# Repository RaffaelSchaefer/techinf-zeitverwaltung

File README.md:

# Techinf Zeitverwaltung

---

## Grundidee

Unsere Idee war es, ein kleines und kompaktes System zu entwickeln, um die Arbeitszeit in Coworking-Spaces oder im Homeoffice zu erfassen.

## Getting Started

### Firmware

Es werden folgende Pakete im Projekt verwendet, die im Nachhinein installiert werden müssen:

- MFRC522
- ArduinoJson

Es müssen ein Verzeichnis namens `.env` erstellt werden. Danach müssen zwei Dateien erstellt werden.

**api.h**

```h
#define API_ADDRESS "Server Adresse"
#define API_KEY "API Passwort"
```

**credentials.h**

```h
#define SSID "SSID"
#define PASSWORD "Passwort"
```

Danach kann `firmware.ino` auf dem ESP 8266 geflasht werden.

### Server

Es gibt zwei Möglichkeiten den Server laufen zulassen. Einmal per Terminal oder via einen Docker Container.

#### Nutzung via Terminal (MacOS/Linux)

**1**: In den Server Ordner wechseln

```bash
cd ./server
```

**2**: Alle Module installieren die gebraucht werden

```bash
pip install -r requirements.txt
```

**3**: Die Datenbank initialisieren

```bash
python main.py -i
```

(**4**: Die Demo Daten hinzufügen)

```bash
python main.py -add
```

**5**: Server starten

```bash
python main.py -a 0.0.0.0 -p [port]
```

#### Nutzung via Docker (MacOS/Linux)

**1**: In den Server Ordner wechseln

```bash
cd ./server
```

**2**: Docker image erstellen

```bash
docker build -t [image_name] .
```

**3**: Docker Container starten

```bash
 docker run -d -p 80:80 --name [container_name] [image_name]
```

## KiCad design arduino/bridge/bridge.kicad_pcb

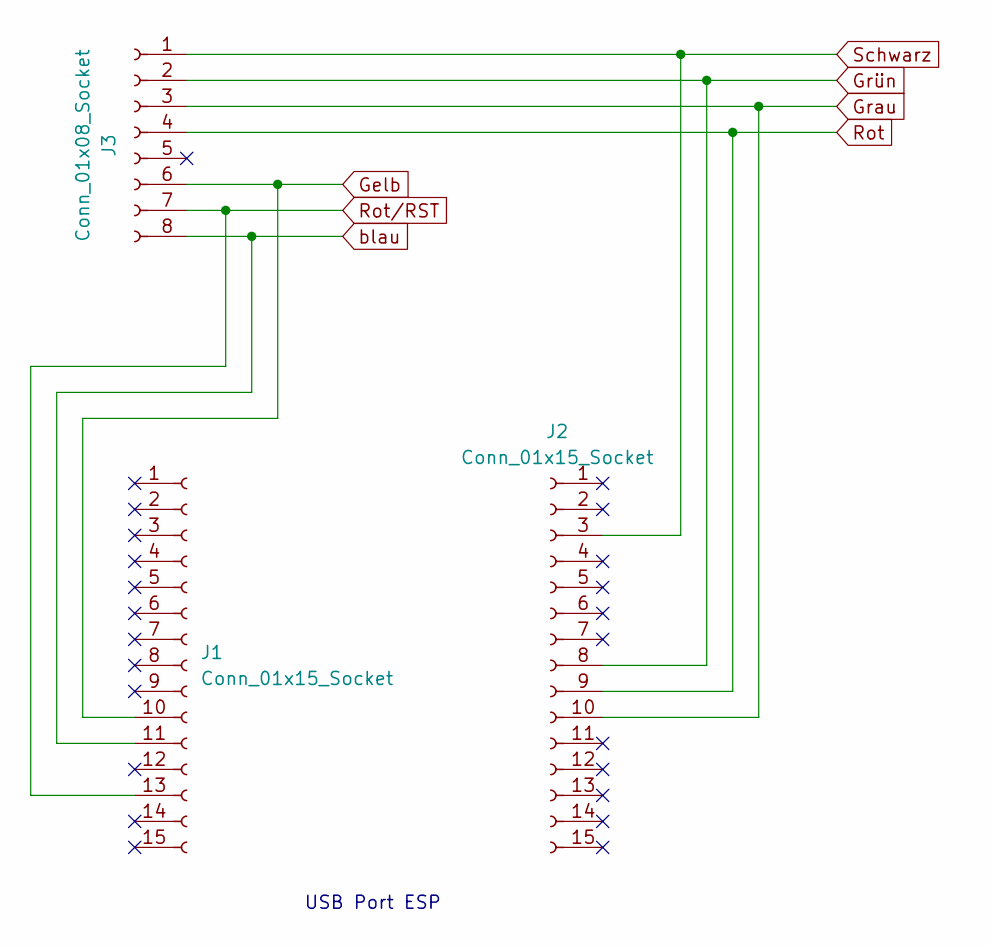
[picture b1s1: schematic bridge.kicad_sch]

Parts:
J1, J2: Conn_01x15_Socket; PinSocket_1x15_P2.54mm_Vertical
J3: Conn_01x08_Socket; PinSocket_1x08_P2.54mm_Vertical

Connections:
Gelb: J1.10, J3.6
Grau: J2.10, J3.3
Grün: J2.8, J3.2
Rot: J2.9, J3.4
Rot/RST: J1.13, J3.7
Schwarz: J2.3, J3.1
blau: J1.11, J3.8

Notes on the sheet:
USB Port ESP

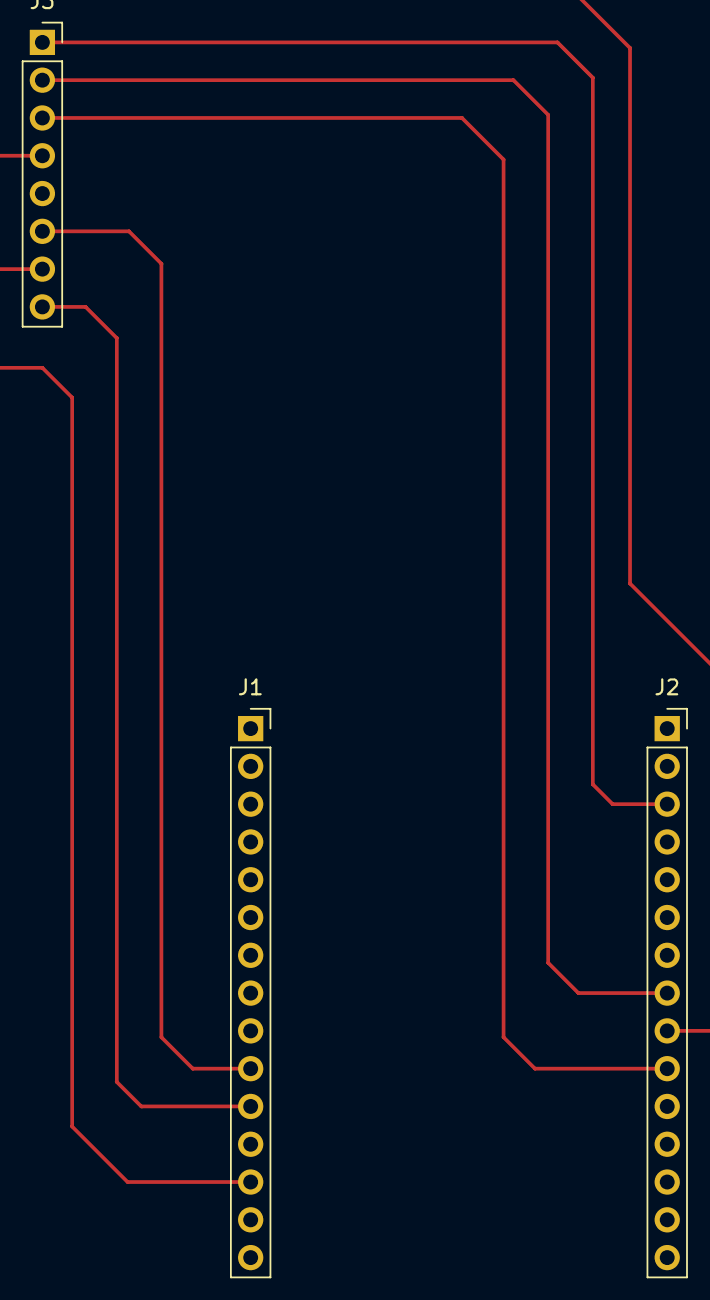
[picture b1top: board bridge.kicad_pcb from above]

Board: 2 copper layers, 3 parts (0 on the bottom side), 7 nets.

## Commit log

2023-12-14 Removed Placeholder and inserted Placeholder
2023-12-19 doc: Added docs
    Imported them as a backup from Overleaf. Please still use the Overleaf Project because this is only a backup
2023-12-19 ref!: Added Template files
    Added Template files for later use
2023-12-21 feat: Added PCB Blueprint
    Added the Blueprint for the bridge component
2023-12-21 feat!: Added test script
2023-12-21 ref: Reformatted Code
2023-12-25 feat: Added Demo capabilities of Server Software
2023-12-25 feat!: Added the first path for the REST API
    Added Flask
2023-12-25 feat: Added Error handling for users route
2023-12-25 feat: Added user path
2023-12-25 ref!: cleaning up the server files
2023-12-26 feat: Added first paths for cards
2023-12-26 ref!: cleaned up args.py
2023-12-26 ref!: Improved visibility of code
2023-12-26 feat: Added insert paths
2023-12-26 feat: Granting of Card Ownership is possible now
    Need further improvements
2023-12-26 feat!: Added Check for card access
    Still needs to throw an Error when it fails
2023-12-26 fix!: Added Error Messages to card access check
2023-12-26 feat!: Opening up the API to the network
2023-12-27 feat!: Added a log path for testing
2023-12-27 ref: optimised imports
2023-12-27 feat: Added active to detail view
2023-12-27 feat!: General improvements
2024-01-02 feat: Added Check for Api Key
    Not very secure but is enough for the project
2024-01-03 feat: Added Api Key to firmware
2024-01-09 feat: Working on pug support
2024-01-10 feat!: pug works
2024-01-10 small fixes
2024-01-10 feat: Server can be used with Docker
2024-01-12 feat!: Added more pages
2024-01-12 feat!: Added delete paths
2024-01-12 feat: All paths complete
2024-01-12 doc: Updated README.md
2024-01-15 Hello World
    Das ist ein test
2024-01-15 feat!: Improved UI
2024-01-15 bridge edit
    pcb and sch edit
2024-01-16 ref!: Removed client folder
    because it no longer needed client is served via server
2024-01-17 add NTPClient and unix epoch time
    add NTPClient and unix epoch time
2024-01-18 feat!: Plots
2024-01-18 epochTime and bridge update
2024-01-19 feat!: Reworking the Database
    Not finished and breaks everything 😎
2024-01-19 feat!: DB v2 should be "complete"
2024-01-20 feat!: UI uses Bootstrap now
2024-01-20 ref!: moved pug files
2024-01-21 feat: Added new paths
2024-01-22 feat!: LOGS!!!!!
    Yippie Fortnite + Cola
2024-01-22 fix: time fix
2024-01-22 feat!: UI v2 done.
2024-01-22 fix: Button bar fix
2024-01-22 fix!: Bug fix
2024-01-25 feat: min time req
    20 sec
2024-02-25 doc: Update
2024-03-08 test: Added a simulator
2024-03-09 Aktualisiere API-Schlüssel in der Simulator-Datei
2024-03-11 doc!: Update
2024-03-11 pdf version
2024-03-12 small fix
